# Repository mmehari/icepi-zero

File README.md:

# Icepi Zero - The portable FPGA development board

| Get your own on: | [**Crowd Supply**](https://www.crowdsupply.com/icy-electronics/icepi-zero)! | [**Elecrow**](https://www.elecrow.com/icepi-zero.html) |
| ---------------- | ------------------------ | ------------------ |

If you are a student/educational institute, send me an email at `cyao _at_ duck.com` and I'll give an educational discount of $65!

We also got a [Discord server](https://discord.gg/vzrqfhcvWr)! Feel free to ask any questions here.

## What is the Icepi Zero?

The Icepi Zero is an FPGA development board in the popular Raspberry Pi Zero form factor. It carries a Lattice ECP5 25F, enabling powerful designs while keeping a small portable size. It also has a GPDI mini (General Purpose Display Interface, same as the one on the Pi Zero) port allowing easy digital video output.

## Why Icepi Zero?

Currently most powerful FPGA boards on the market are expensive and bulky.

I've always wanted a low-cost portable FPGA with video output to make my own CPU, but there isn't any on the market.

The Icepi Zero aims to fix this. Carrying a powerful ECP5 FPGA on a small Raspberry Pi Zero form factor, it is the ultimate portable solution for FPGA development. Additionally packing a GPDI mini port and 3 USB-C ports, it allows interfacing with multiple external I/O devices.

Icepi Zero is for everyone: Students can use it to learn about the internals of modern processors. Gamers can use it to emulate old hardware. Programmers can use it to test their code on multiple architectures.

<sub>Oberon running on Icepi Zero</sub>

Icepi Zero also has an on-board USB to JTAG converter, so no external programmers are needed.

Moreover Icepi Zero is fully open-source, no strings attached. Learn from the design! ([OSHWA cerified FR000026](https://certification.oshwa.org/fr000026.html)).

## Features

- Raspberry Pi Zero form factor
- Lattice ECP5U FPGA:
    - 24k LUT
    - 112 KiB of RAM
- One MiniGPDI connector (it's HDM- but I don't have the money to buy a license...)
- Three USB-C Ports
- 256Mbit 166MHz SDRAM
- MicroSD card slot
- On-board USB to JTAG and UART converter
- 50MHz external oscillator
- 128 Mbit of flash
- 4 user LEDs
- 2 user buttons

This powerful configuration allows the PCB to be used in numerous ways, including real time video processing, hardware AI acceleration and prototyping of ASICs. 

## Emulation

Over the course of multiple weeks, multiple emulation cores have been ported over, such as the [Oberon](https://github.com/cheyao/oberon), [Apple I](https://github.com/cheyao/apple-one) and the [Acorn Atom](https://github.com/cheyao/acorn_atom)! The Icepi Zero allows you to take cycle accurate replicas of your favourite systems in your pocket.

<sub>Apple I running on the Icepi</sub>

<sub>Acorn Atom running on the Icepi</sub>

## Learning

It is also supported by icestudio (custom fork: https://github.com/cheyao/icestudio), allowing easy access for beginners.

## Usage

Check out the `firmware` folder for example code and compilation instructions!

If you want to order this board, it uses a 1.2mm/1.6mm PCB with JLC04121H-7628 Stackup. Gerbers are in the `production` folder in the `hardware` directory.

For the PCB, the smallest component size is 0201 for 27 Ohm resistors on the USB-C datalines. But if you want only 0402 components, just delete those 0201 resistors and you will be fine.

NOTE: If you fabbed v1.1 before 01/06, the pins of the USB pullups and LED0 is different - check your gerbers.

[View PCB online](https://kicanvas.org/?github=https%3A%2F%2Fgithub.com%2Fcheyao%2Ficepi-zero%2Ftree%2Fmain%2Fhardware%2Fv1.2)

## Acknowledgments

This project was inspired by the [ulx3s](https://github.com/emard/ulx3s), huge props to the ulx3s team for making such a good board!

## Contact

If there is any questions DM `cyao.` or join the [discord server](https://discord.gg/vzrqfhcvWr)! Feel free to ask any questions here. Mail is also accepted at `cyao _at_ duck.com`. :)

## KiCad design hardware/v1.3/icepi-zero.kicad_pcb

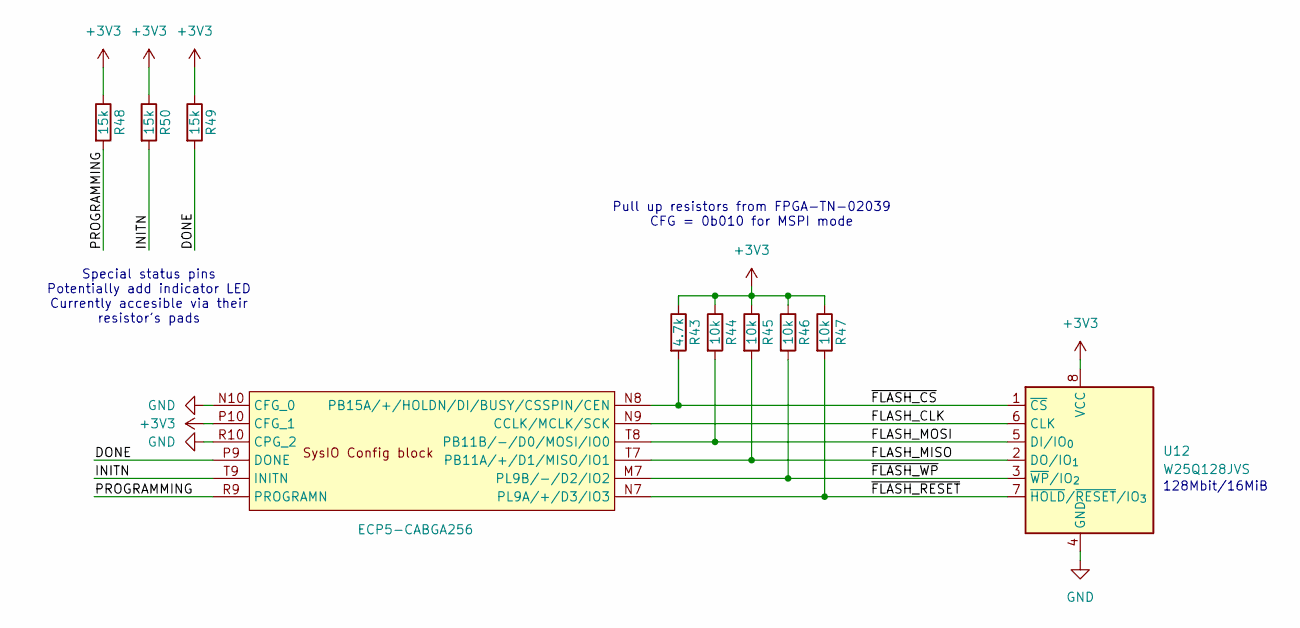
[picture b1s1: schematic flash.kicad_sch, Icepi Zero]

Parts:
R43: 4.7k; R_0402_1005Metric; Manufactuer Part Number 0402WGF4701TCE; LCSC Part # C25900
R44, R45, R46, R47: 10k; R_0402_1005Metric; Manufactuer Part Number 0402WGF1002TCE; LCSC Part # C25744
R48, R49, R50: 15k; R_0402_1005Metric; Manufactuer Part Number 0402WGF1502TCE; LCSC Part # C25756
U1: ECP5-CABGA256; BGA-256_14.0x14.0mm_Layout16x16_P0.8mm_Ball0.45mm_Pad0.32mm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; Manufactuer Part Number LFE5U-25F-6BG256C; LCSC Part # C1521614
U12: W25Q128JVS; SOIC-8_5.3x5.3mm_P1.27mm; Manufactuer Part Number W25Q128JVSIQ; LCSC Part # C97521

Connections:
+3V3: R43.1, R44.1, R45.1, R46.1, R47.1, R48.1, R49.1, R50.1, U1.P10 (CFG_1), U12.8 (VCC); also elsewhere on the board
/DBG1: U1.C7 (PT27A/+/PCLKT0_1); also elsewhere on the board
/DBG2: U1.C8 (PT35A/+/PCLKT1_0); also elsewhere on the board
/Flash/DONE: R49.2, U1.P9 (DONE)
/Flash/FLASH_CLK: U1.N9 (CCLK/MCLK/SCK), U12.6 (CLK)
/Flash/FLASH_MISO: R45.2, U1.T7 (PB11A/+/D1/MISO/IO1), U12.2 (DO/IO_{1})
/Flash/FLASH_MOSI: R44.2, U1.T8 (PB11B/-/D0/MOSI/IO0), U12.5 (DI/IO_{0})
/Flash/INITN: R50.2, U1.T9 (INITN)
/Flash/PROGRAMMING: R48.2, U1.R9 (PROGRAMN)
/Flash/~FLASH_CS: R43.2, U1.N8 (PB15A/+/HOLDN/DI/BUSY/CSSPIN/CEN), U12.1 (~CS)
/Flash/~FLASH_RESET: R47.2, U1.N7 (PL9A/+/D3/IO3), U12.7 (~HOLD/~RESET/IO_{3})
/Flash/~FLASH_WP: R46.2, U1.M7 (PL9B/-/D2/IO2), U12.3 (~WP/IO_{2})
/GLOBAL_CLK: U1.M1 (PL26C/+/LDQ32/PCLKT6_0); also elsewhere on the board
/GPIO0: U1.G3 (PL14C/+/LDQ20/VREF1_7); also elsewhere on the board
/GPIO1: U1.K3 (PL20D/-/LDQS20); also elsewhere on the board
/GPIO2: U1.T2 (PL38D/-/LDQ44); also elsewhere on the board
/GPIO3: U1.R2 (PL38C/+/LDQ44); also elsewhere on the board
/GPIO4: U1.R1 (PL35B/-/HS/LDQ32/VREF1_6); also elsewhere on the board
/GPIO5: U1.E1 (PL11D/-/LDQ8); also elsewhere on the board
/GPIO6: U1.F3 (PL5D/-/LDQ8); also elsewhere on the board
/GPIO7: U1.G1 (PL20A/+/HS/LDQS20/GR_PCLK7_1); also elsewhere on the board
/GPIO8: U1.H2 (PL20C/+/LDQS20/GR_PCLK7_0); also elsewhere on the board
/GPIO9: U1.J1 (PL23A/+/HS/LDQ20/PCLKT7); also elsewhere on the board
/GPIO10: U1.L2 (PL26B/-/HS/LDQ32/PCLKC6_1); also elsewhere on the board
/GPIO11: U1.G2 (PL14B/-/HS/LDQ20); also elsewhere on the board
/GPIO12: U1.J3 (PL20B/-/HS/LDQSN20); also elsewhere on the board
/GPIO13: U1.E3 (PL5C/+/LDQ8); also elsewhere on the board
/GPIO14: U1.P1 (PL35A/+/HS/LDQ32); also elsewhere on the board
/GPIO15: U1.N1 (PL32A/+/HS/LDQS32); also elsewhere on the board
/GPIO16: U1.H3 (PL14D/-/lDQ20); also elsewhere on the board
/GPIO17: U1.R3 (PL41B/-/HS/LDQ44); also elsewhere on the board
/GPIO18: U1.N4 (PL38A/+/HS/LDQ44); also elsewhere on the board
/GPIO19: U1.E4 (PT9A/+); also elsewhere on the board
/GPIO20: U1.F1 (PL14A/+/HS/LDQ20); also elsewhere on the board
/GPIO21: U1.F2 (PL11C/+/LDQ8); also elsewhere on the board
/GPIO22: U1.P2 (PL32B/-/HS/LDQSN32); also elsewhere on the board
/GPIO23: U1.M2 (PL26D/-/LDQ32/PCLK6_0); also elsewhere on the board
/GPIO24: U1.L1 (PL26A/+/HS/LDQ32/PCLKT6_1); also elsewhere on the board
/GPIO25: U1.J2 (PL23B/-/HS/LDQ20/PCLKC7_1); also elsewhere on the board
/GPIO26: U1.D4 (PT9B/-); also elsewhere on the board
/GPIO27: U1.P3 (PL38B/-/HS/LDQ44); also elsewhere on the board
/LED0: U1.E13 (PT62B/-); also elsewhere on the board
/LED1: U1.D14 (PR2D/-/RDQ8); also elsewhere on the board
/LED2: U1.E12 (PT58B/-); also elsewhere on the board
/LED3: U1.C13 (PT60B/-); also elsewhere on the board
/LED4: U1.D13 (PT62A/+); also elsewhere on the board
/SW0: U1.C4 (PT11A/+); also elsewhere on the board
/SW1: U1.C5 (PT15A/+); also elsewhere on the board
GND: U1.N10 (CFG_0), U1.R10 (CPG_2), U12.4 (GND); also elsewhere on the board

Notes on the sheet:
128Mbit/16MiB
Special status pins Potentially add indicator LED Currently accesible via their resistor's pads
Pull up resistors from FPGA-TN-02039 CFG = 0b010 for MSPI mode

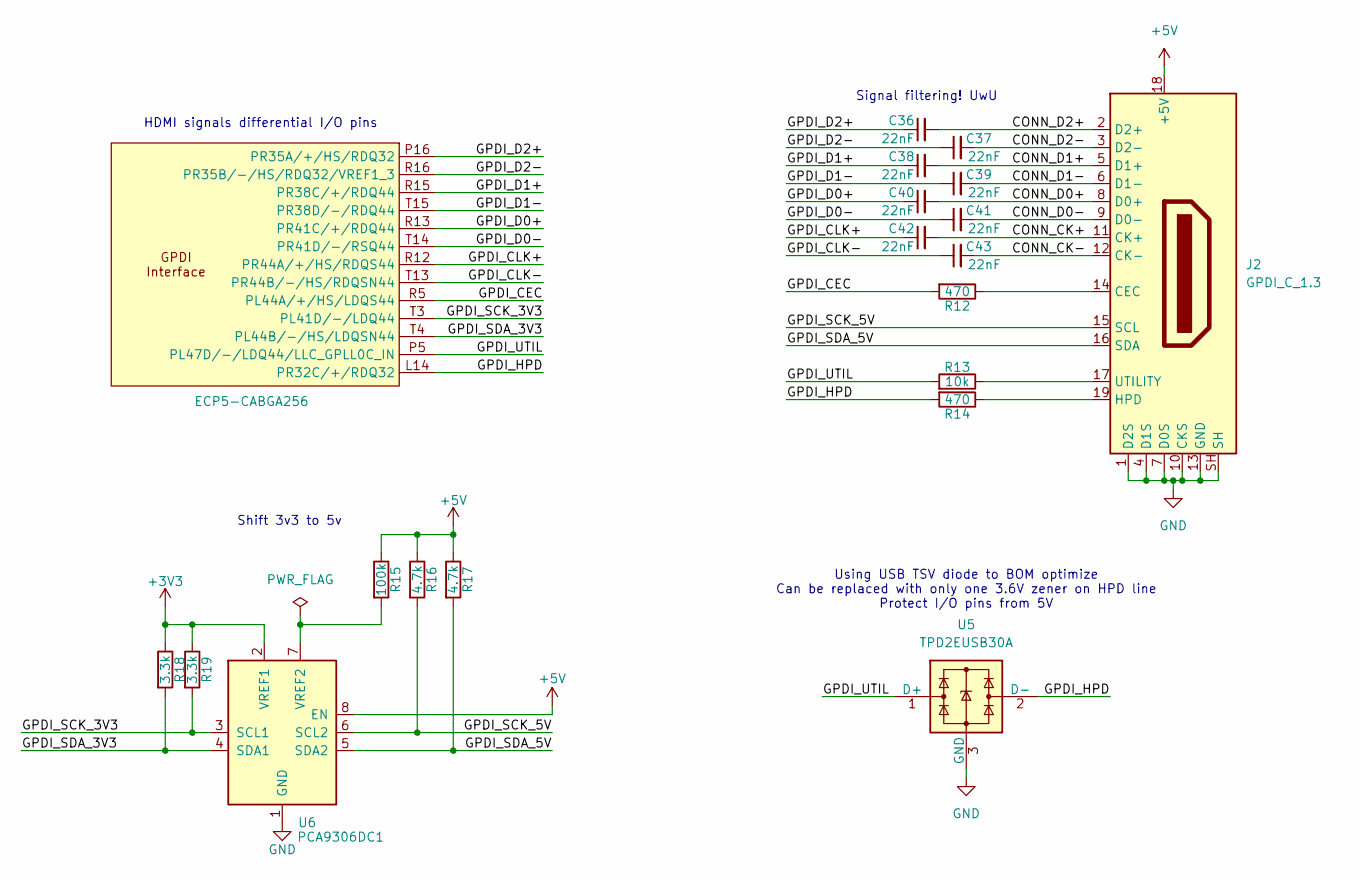
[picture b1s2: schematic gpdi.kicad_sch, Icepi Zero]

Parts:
C36, C37, C38, C39, C40, C41, C42, C43: 22nF; C_0402_1005Metric; Manufactuer Part Number 0402B223K500NT; LCSC Part # C1532
J2: GPDI_C_1.3; XKB Connection A71-05H4-111N1; Manufactuer Part Number A71-05H4-111N1; LCSC Part # C2682170
R12, R14: 470; R_0402_1005Metric; Manufactuer Part Number 0402WGF4700TCE; LCSC Part # C25117
R13: 10k; R_0402_1005Metric; Manufactuer Part Number 0402WGF1002TCE; LCSC Part # C25744
R15: 100k; R_0402_1005Metric; Manufactuer Part Number 0402WGF1003TCE; LCSC Part # C25741
R16, R17: 4.7k; R_0402_1005Metric; Manufactuer Part Number 0402WGF4701TCE; LCSC Part # C25900
R18, R19: 3.3k; R_0402_1005Metric; Manufactuer Part Number 0402WGF3301TCE; LCSC Part # C25890
U1: ECP5-CABGA256; BGA-256_14.0x14.0mm_Layout16x16_P0.8mm_Ball0.45mm_Pad0.32mm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; Manufactuer Part Number LFE5U-25F-6BG256C; LCSC Part # C1521614
U5: TPD2EUSB30A; Texas_DRT-3; Manufactuer Part Number TPD2EUSB30ADRTR; LCSC Part # C3011197
U6: PCA9306DC1; VSSOP-8_2.3x2mm_P0.5mm; Manufactuer Part Number PCA9306DC1; LCSC Part # C129510

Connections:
+3V3: R18.1, R19.1, U6.2 (VREF1); also elsewhere on the board
+5V: J2.18 (+5V), R15.1, R16.1, R17.1, U6.8 (EN); also elsewhere on the board
/DBG1: U1.C7 (PT27A/+/PCLKT0_1); also elsewhere on the board
/DBG2: U1.C8 (PT35A/+/PCLKT1_0); also elsewhere on the board
/GLOBAL_CLK: U1.M1 (PL26C/+/LDQ32/PCLKT6_0); also elsewhere on the board
/GPDI/CONN_CK+: C42.2, J2.11 (CK+)
/GPDI/CONN_CK-: C43.2, J2.12 (CK-)
/GPDI/CONN_D0+: C40.2, J2.8 (D0+)
/GPDI/CONN_D0-: C41.2, J2.9 (D0-)
/GPDI/CONN_D1+: C38.2, J2.5 (D1+)
/GPDI/CONN_D1-: C39.2, J2.6 (D1-)
/GPDI/CONN_D2+: C36.2, J2.2 (D2+)
/GPDI/CONN_D2-: C37.2, J2.3 (D2-)
/GPDI/GPDI_CEC: R12.2, U1.R5 (PL44A/+/HS/LDQS44)
/GPDI/GPDI_CLK+: C42.1, U1.R12 (PR44A/+/HS/RDQS44)
/GPDI/GPDI_CLK-: C43.1, U1.T13 (PR44B/-/HS/RDQSN44)
/GPDI/GPDI_D0+: C40.1, U1.R13 (PR41C/+/RDQ44)
/GPDI/GPDI_D0-: C41.1, U1.T14 (PR41D/-/RSQ44)
/GPDI/GPDI_D1+: C38.1, U1.R15 (PR38C/+/RDQ44)
/GPDI/GPDI_D1-: C39.1, U1.T15 (PR38D/-/RDQ44)
/GPDI/GPDI_D2+: C36.1, U1.P16 (PR35A/+/HS/RDQ32)
/GPDI/GPDI_D2-: C37.1, U1.R16 (PR35B/-/HS/RDQ32/VREF1_3)
/GPDI/GPDI_HPD: R14.2, U1.L14 (PR32C/+/RDQ32), U5.2 (D-)
/GPDI/GPDI_SCK_3V3: R19.2, U1.T3 (PL41D/-/LDQ44), U6.3 (SCL1)
/GPDI/GPDI_SCK_5V: J2.15 (SCL), R16.2, U6.6 (SCL2)
/GPDI/GPDI_SDA_3V3: R18.2, U1.T4 (PL44B/-/HS/LDQSN44), U6.4 (SDA1)
/GPDI/GPDI_SDA_5V: J2.16 (SDA), R17.2, U6.5 (SDA2)
/GPDI/GPDI_UTIL: R13.2, U1.P5 (PL47D/-/LDQ44/LLC_GPLL0C_IN), U5.1 (D+)
/GPIO0: U1.G3 (PL14C/+/LDQ20/VREF1_7); also elsewhere on the board
/GPIO1: U1.K3 (PL20D/-/LDQS20); also elsewhere on the board
/GPIO2: U1.T2 (PL38D/-/LDQ44); also elsewhere on the board
/GPIO3: U1.R2 (PL38C/+/LDQ44); also elsewhere on the board
/GPIO4: U1.R1 (PL35B/-/HS/LDQ32/VREF1_6); also elsewhere on the board
/GPIO5: U1.E1 (PL11D/-/LDQ8); also elsewhere on the board
/GPIO6: U1.F3 (PL5D/-/LDQ8); also elsewhere on the board
/GPIO7: U1.G1 (PL20A/+/HS/LDQS20/GR_PCLK7_1); also elsewhere on the board
/GPIO8: U1.H2 (PL20C/+/LDQS20/GR_PCLK7_0); also elsewhere on the board
/GPIO9: U1.J1 (PL23A/+/HS/LDQ20/PCLKT7); also elsewhere on the board
/GPIO10: U1.L2 (PL26B/-/HS/LDQ32/PCLKC6_1); also elsewhere on the board
/GPIO11: U1.G2 (PL14B/-/HS/LDQ20); also elsewhere on the board
/GPIO12: U1.J3 (PL20B/-/HS/LDQSN20); also elsewhere on the board
/GPIO13: U1.E3 (PL5C/+/LDQ8); also elsewhere on the board
/GPIO14: U1.P1 (PL35A/+/HS/LDQ32); also elsewhere on the board
/GPIO15: U1.N1 (PL32A/+/HS/LDQS32); also elsewhere on the board
/GPIO16: U1.H3 (PL14D/-/lDQ20); also elsewhere on the board
/GPIO17: U1.R3 (PL41B/-/HS/LDQ44); also elsewhere on the board
/GPIO18: U1.N4 (PL38A/+/HS/LDQ44); also elsewhere on the board
/GPIO19: U1.E4 (PT9A/+); also elsewhere on the board
/GPIO20: U1.F1 (PL14A/+/HS/LDQ20); also elsewhere on the board
/GPIO21: U1.F2 (PL11C/+/LDQ8); also elsewhere on the board
/GPIO22: U1.P2 (PL32B/-/HS/LDQSN32); also elsewhere on the board
/GPIO23: U1.M2 (PL26D/-/LDQ32/PCLK6_0); also elsewhere on the board
/GPIO24: U1.L1 (PL26A/+/HS/LDQ32/PCLKT6_1); also elsewhere on the board
/GPIO25: U1.J2 (PL23B/-/HS/LDQ20/PCLKC7_1); also elsewhere on the board
/GPIO26: U1.D4 (PT9B/-); also elsewhere on the board
/GPIO27: U1.P3 (PL38B/-/HS/LDQ44); also elsewhere on the board
/LED0: U1.E13 (PT62B/-); also elsewhere on the board
/LED1: U1.D14 (PR2D/-/RDQ8); also elsewhere on the board
/LED2: U1.E12 (PT58B/-); also elsewhere on the board
/LED3: U1.C13 (PT60B/-); also elsewhere on the board
/LED4: U1.D13 (PT62A/+); also elsewhere on the board
/SW0: U1.C4 (PT11A/+); also elsewhere on the board
/SW1: U1.C5 (PT15A/+); also elsewhere on the board
GND: J2.1 (D2S), J2.4 (D1S), J2.7 (D0S), J2.10 (CKS), J2.13 (GND), J2.SH, U5.3 (GND), U6.1 (GND); also elsewhere on the board
unnamed: J2.14 (CEC), R12.1
unnamed: J2.19 (HPD), R14.1
unnamed: J2.17 (UTILITY), R13.1
unnamed: R15.2, U6.7 (VREF2)

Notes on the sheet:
Shift 3v3 to 5v
Using USB TSV diode to BOM optimize Can be replaced with only one 3.6V zener on HPD line Protect I/O pins from 5V
HDMI signals differential I/O pins
Signal filtering! UwU

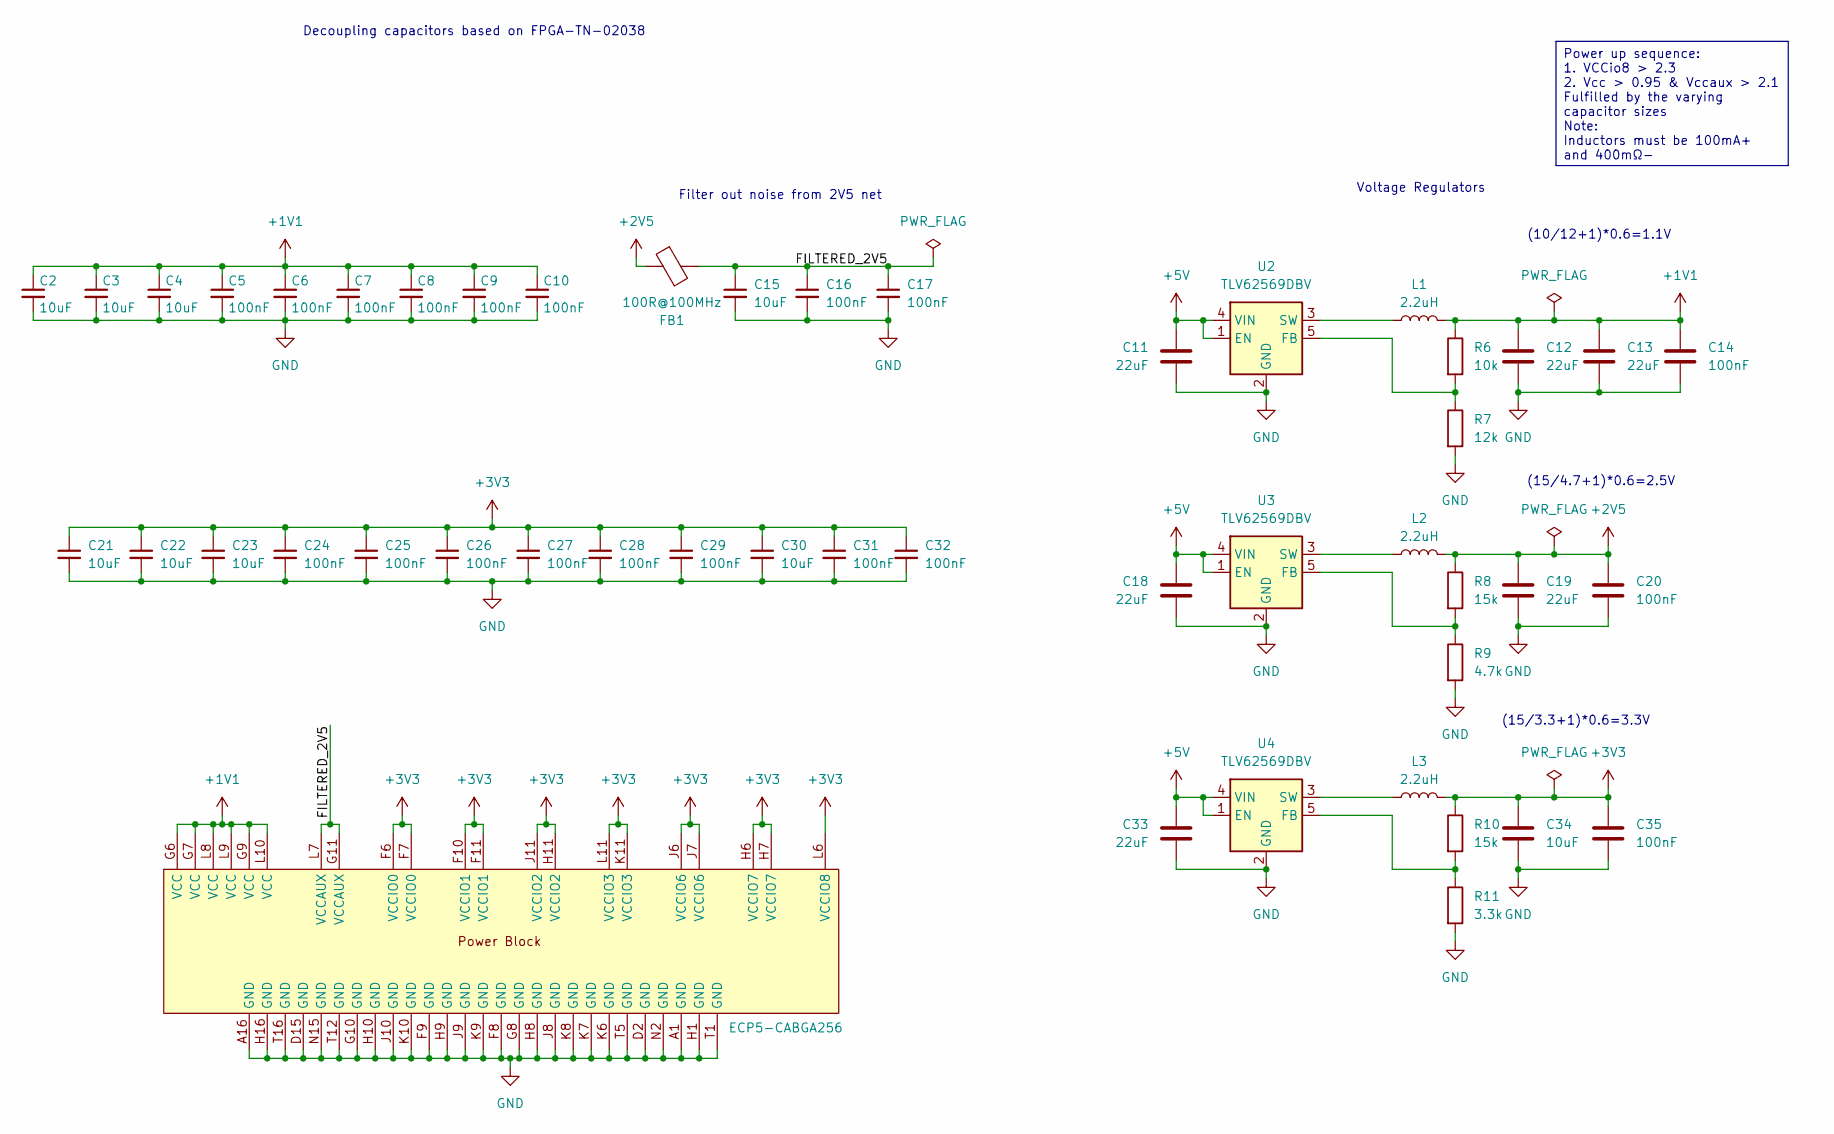
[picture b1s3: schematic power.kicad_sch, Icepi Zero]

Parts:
C2, C3, C4, C15, C21, C22, C23, C30, C34: 10uF; C_0603_1608Metric; Manufactuer Part Number CL10A106KP8NNNC; LCSC Part # C19702
C5, C6, C7, C8, C9, C10, C14, C16, C17, C20, C24, C25, C26, C27, C28, C29, C31, C32, C35: 100nF; C_0402_1005Metric; Manufactuer Part Number CL05B104KB54PNC; LCSC Part # C307331
C11, C12, C13, C18, C19, C33: 22uF; C_0603_1608Metric; Manufactuer Part Number CL10A226MQ8NRNC; LCSC Part # C59461
FB1: 100R@100MHz; L_0805_2012Metric; Manufactuer Part Number CBG201209U101T; LCSC Part # C74480
L1, L2, L3: 2.2uH; L_0805_2012Metric; Manufactuer Part Number TDK MLP2012S2R2MT0S1; LCSC Part # C107322
R6: 10k; R_0402_1005Metric; Manufactuer Part Number 0402WGF1002TCE; LCSC Part # C25744
R7: 12k; R_0402_1005Metric; Manufactuer Part Number 0402WGF1202TCE; LCSC Part # C25752
R8, R10: 15k; R_0402_1005Metric; Manufactuer Part Number 0402WGF1502TCE; LCSC Part # C25756
R9: 4.7k; R_0402_1005Metric; Manufactuer Part Number 0402WGF4701TCE; LCSC Part # C25900
R11: 3.3k; R_0402_1005Metric; Manufactuer Part Number 0402WGF3301TCE; LCSC Part # C25890
U1: ECP5-CABGA256; BGA-256_14.0x14.0mm_Layout16x16_P0.8mm_Ball0.45mm_Pad0.32mm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; Manufactuer Part Number LFE5U-25F-6BG256C; LCSC Part # C1521614
U2, U3, U4: TLV62569DBV; SOT-23-5; Manufactuer Part Number TLV62569DBVR; LCSC Part # C141836

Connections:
+1V1: C2.1, C3.1, C4.1, C5.1, C6.1, C7.1, C8.1, C9.1, C10.1, C12.1, C13.1, C14.1, L1.2, R6.1, U1.G6 (VCC), U1.G7 (VCC), U1.G9 (VCC), U1.L8 (VCC), U1.L9 (VCC), U1.L10 (VCC); also elsewhere on the board
+2V5: C19.1, C20.1, FB1.1, L2.2, R8.1; also elsewhere on the board
+3V3: C21.1, C22.1, C23.1, C24.1, C25.1, C26.1, C27.1, C28.1, C29.1, C30.1, C31.1, C32.1, C34.1, C35.1, L3.2, R10.1, U1.F6 (VCCIO0), U1.F7 (VCCIO0), U1.F10 (VCCIO1), U1.F11 (VCCIO1), U1.H6 (VCCIO7), U1.H7 (VCCIO7), U1.H11 (VCCIO2), U1.J6 (VCCIO6), U1.J7 (VCCIO6), U1.J11 (VCCIO2), U1.K11 (VCCIO3), U1.L6 (VCCIO8), U1.L11 (VCCIO3); also elsewhere on the board
+5V: C11.1, C18.1, C33.1, U2.1 (EN), U2.4 (VIN), U3.1 (EN), U3.4 (VIN), U4.1 (EN), U4.4 (VIN); also elsewhere on the board
/DBG1: U1.C7 (PT27A/+/PCLKT0_1); also elsewhere on the board
/DBG2: U1.C8 (PT35A/+/PCLKT1_0); also elsewhere on the board
/GLOBAL_CLK: U1.M1 (PL26C/+/LDQ32/PCLKT6_0); also elsewhere on the board
/GPIO0: U1.G3 (PL14C/+/LDQ20/VREF1_7); also elsewhere on the board
/GPIO1: U1.K3 (PL20D/-/LDQS20); also elsewhere on the board
/GPIO2: U1.T2 (PL38D/-/LDQ44); also elsewhere on the board
/GPIO3: U1.R2 (PL38C/+/LDQ44); also elsewhere on the board
/GPIO4: U1.R1 (PL35B/-/HS/LDQ32/VREF1_6); also elsewhere on the board
/GPIO5: U1.E1 (PL11D/-/LDQ8); also elsewhere on the board
/GPIO6: U1.F3 (PL5D/-/LDQ8); also elsewhere on the board
/GPIO7: U1.G1 (PL20A/+/HS/LDQS20/GR_PCLK7_1); also elsewhere on the board
/GPIO8: U1.H2 (PL20C/+/LDQS20/GR_PCLK7_0); also elsewhere on the board
/GPIO9: U1.J1 (PL23A/+/HS/LDQ20/PCLKT7); also elsewhere on the board
/GPIO10: U1.L2 (PL26B/-/HS/LDQ32/PCLKC6_1); also elsewhere on the board
/GPIO11: U1.G2 (PL14B/-/HS/LDQ20); also elsewhere on the board
/GPIO12: U1.J3 (PL20B/-/HS/LDQSN20); also elsewhere on the board
/GPIO13: U1.E3 (PL5C/+/LDQ8); also elsewhere on the board
/GPIO14: U1.P1 (PL35A/+/HS/LDQ32); also elsewhere on the board
/GPIO15: U1.N1 (PL32A/+/HS/LDQS32); also elsewhere on the board
/GPIO16: U1.H3 (PL14D/-/lDQ20); also elsewhere on the board
/GPIO17: U1.R3 (PL41B/-/HS/LDQ44); also elsewhere on the board
/GPIO18: U1.N4 (PL38A/+/HS/LDQ44); also elsewhere on the board
/GPIO19: U1.E4 (PT9A/+); also elsewhere on the board
/GPIO20: U1.F1 (PL14A/+/HS/LDQ20); also elsewhere on the board
/GPIO21: U1.F2 (PL11C/+/LDQ8); also elsewhere on the board
/GPIO22: U1.P2 (PL32B/-/HS/LDQSN32); also elsewhere on the board
/GPIO23: U1.M2 (PL26D/-/LDQ32/PCLK6_0); also elsewhere on the board
/GPIO24: U1.L1 (PL26A/+/HS/LDQ32/PCLKT6_1); also elsewhere on the board
/GPIO25: U1.J2 (PL23B/-/HS/LDQ20/PCLKC7_1); also elsewhere on the board
/GPIO26: U1.D4 (PT9B/-); also elsewhere on the board
/GPIO27: U1.P3 (PL38B/-/HS/LDQ44); also elsewhere on the board
/LED0: U1.E13 (PT62B/-); also elsewhere on the board
/LED1: U1.D14 (PR2D/-/RDQ8); also elsewhere on the board
/LED2: U1.E12 (PT58B/-); also elsewhere on the board
/LED3: U1.C13 (PT60B/-); also elsewhere on the board
/LED4: U1.D13 (PT62A/+); also elsewhere on the board
/Power/FILTERED_2V5: C15.1, C16.1, C17.1, FB1.2, U1.G11 (VCCAUX), U1.L7 (VCCAUX)
/SW0: U1.C4 (PT11A/+); also elsewhere on the board
/SW1: U1.C5 (PT15A/+); also elsewhere on the board
GND: C2.2, C3.2, C4.2, C5.2, C6.2, C7.2, C8.2, C9.2, C10.2, C11.2, C12.2, C13.2, C14.2, C15.2, C16.2, C17.2, C18.2, C19.2, C20.2, C21.2, C22.2, C23.2, C24.2, C25.2, C26.2, C27.2, C28.2, C29.2, C30.2, C31.2, C32.2, C33.2, C34.2, C35.2, R7.2, R9.2, R11.2, U1.A1 (GND), U1.A16 (GND), U1.D2 (GND), U1.D15 (GND), U1.F8 (GND), U1.F9 (GND), U1.G8 (GND), U1.G10 (GND), U1.H1 (GND), U1.H8 (GND), U1.H9 (GND), U1.H10 (GND), U1.H16 (GND), U1.J8 (GND), U1.J9 (GND), U1.J10 (GND), U1.K6 (GND), U1.K7 (GND), U1.K8 (GND), U1.K9 (GND), U1.K10 (GND), U1.N2 (GND), U1.N15 (GND), U1.T1 (GND), U1.T5 (GND), U1.T12 (GND), U1.T16 (GND), U2.2 (GND), U3.2 (GND), U4.2 (GND); also elsewhere on the board
unnamed: R6.2, R7.1, U2.5 (FB)
unnamed: L1.1, U2.3 (SW)
unnamed: R8.2, R9.1, U3.5 (FB)
unnamed: L2.1, U3.3 (SW)
unnamed: R10.2, R11.1, U4.5 (FB)
unnamed: L3.1, U4.3 (SW)

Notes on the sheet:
Decoupling capacitors based on FPGA-TN-02038
(15/4.7+1)*0.6=2.5V
(10/12+1)*0.6=1.1V
Filter out noise from 2V5 net
(15/3.3+1)*0.6=3.3V
Voltage Regulators
Power up sequence: 1. VCCio8 > 2.3 2. Vcc > 0.95 & Vccaux > 2.1 Fulfilled by the varying capacitor sizes Note: Inductors must be 100mA+ and 400mΩ-

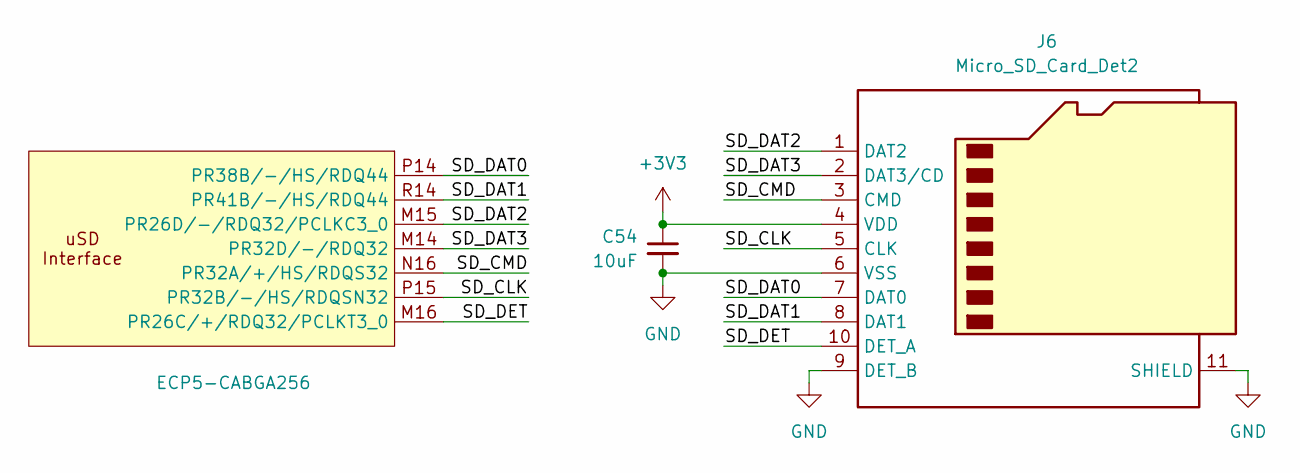
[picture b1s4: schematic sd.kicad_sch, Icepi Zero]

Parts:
C54: 10uF; C_0603_1608Metric; Manufactuer Part Number CL10A106KP8NNNC; LCSC Part # C19702
J6: Micro_SD_Card_Det2; microSD_HC_SOFNG_TF-008; Manufactuer Part Number TF-008; LCSC Part # C428465
U1: ECP5-CABGA256; BGA-256_14.0x14.0mm_Layout16x16_P0.8mm_Ball0.45mm_Pad0.32mm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; Manufactuer Part Number LFE5U-25F-6BG256C; LCSC Part # C1521614

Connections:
+3V3: C54.1, J6.4 (VDD); also elsewhere on the board
/DBG1: U1.C7 (PT27A/+/PCLKT0_1); also elsewhere on the board
/DBG2: U1.C8 (PT35A/+/PCLKT1_0); also elsewhere on the board
/GLOBAL_CLK: U1.M1 (PL26C/+/LDQ32/PCLKT6_0); also elsewhere on the board
/GPIO0: U1.G3 (PL14C/+/LDQ20/VREF1_7); also elsewhere on the board
/GPIO1: U1.K3 (PL20D/-/LDQS20); also elsewhere on the board
/GPIO2: U1.T2 (PL38D/-/LDQ44); also elsewhere on the board
/GPIO3: U1.R2 (PL38C/+/LDQ44); also elsewhere on the board
/GPIO4: U1.R1 (PL35B/-/HS/LDQ32/VREF1_6); also elsewhere on the board
/GPIO5: U1.E1 (PL11D/-/LDQ8); also elsewhere on the board
/GPIO6: U1.F3 (PL5D/-/LDQ8); also elsewhere on the board
/GPIO7: U1.G1 (PL20A/+/HS/LDQS20/GR_PCLK7_1); also elsewhere on the board
/GPIO8: U1.H2 (PL20C/+/LDQS20/GR_PCLK7_0); also elsewhere on the board
/GPIO9: U1.J1 (PL23A/+/HS/LDQ20/PCLKT7); also elsewhere on the board
/GPIO10: U1.L2 (PL26B/-/HS/LDQ32/PCLKC6_1); also elsewhere on the board
/GPIO11: U1.G2 (PL14B/-/HS/LDQ20); also elsewhere on the board
/GPIO12: U1.J3 (PL20B/-/HS/LDQSN20); also elsewhere on the board
/GPIO13: U1.E3 (PL5C/+/LDQ8); also elsewhere on the board
/GPIO14: U1.P1 (PL35A/+/HS/LDQ32); also elsewhere on the board
/GPIO15: U1.N1 (PL32A/+/HS/LDQS32); also elsewhere on the board
/GPIO16: U1.H3 (PL14D/-/lDQ20); also elsewhere on the board
/GPIO17: U1.R3 (PL41B/-/HS/LDQ44); also elsewhere on the board
/GPIO18: U1.N4 (PL38A/+/HS/LDQ44); also elsewhere on the board
/GPIO19: U1.E4 (PT9A/+); also elsewhere on the board
/GPIO20: U1.F1 (PL14A/+/HS/LDQ20); also elsewhere on the board
/GPIO21: U1.F2 (PL11C/+/LDQ8); also elsewhere on the board
/GPIO22: U1.P2 (PL32B/-/HS/LDQSN32); also elsewhere on the board
/GPIO23: U1.M2 (PL26D/-/LDQ32/PCLK6_0); also elsewhere on the board
/GPIO24: U1.L1 (PL26A/+/HS/LDQ32/PCLKT6_1); also elsewhere on the board
/GPIO25: U1.J2 (PL23B/-/HS/LDQ20/PCLKC7_1); also elsewhere on the board
/GPIO26: U1.D4 (PT9B/-); also elsewhere on the board
/GPIO27: U1.P3 (PL38B/-/HS/LDQ44); also elsewhere on the board
/LED0: U1.E13 (PT62B/-); also elsewhere on the board
/LED1: U1.D14 (PR2D/-/RDQ8); also elsewhere on the board
/LED2: U1.E12 (PT58B/-); also elsewhere on the board
/LED3: U1.C13 (PT60B/-); also elsewhere on the board
/LED4: U1.D13 (PT62A/+); also elsewhere on the board
/SW0: U1.C4 (PT11A/+); also elsewhere on the board
/SW1: U1.C5 (PT15A/+); also elsewhere on the board
/uSD/SD_CLK: J6.5 (CLK), U1.P15 (PR32B/-/HS/RDQSN32)
/uSD/SD_CMD: J6.3 (CMD), U1.N16 (PR32A/+/HS/RDQS32)
/uSD/SD_DAT0: J6.7 (DAT0), U1.P14 (PR38B/-/HS/RDQ44)
/uSD/SD_DAT1: J6.8 (DAT1), U1.R14 (PR41B/-/HS/RDQ44)
/uSD/SD_DAT2: J6.1 (DAT2), U1.M15 (PR26D/-/RDQ32/PCLKC3_0)
/uSD/SD_DAT3: J6.2 (DAT3/CD), U1.M14 (PR32D/-/RDQ32)
/uSD/SD_DET: J6.10 (DET_A), U1.M16 (PR26C/+/RDQ32/PCLKT3_0)
GND: C54.2, J6.6 (VSS), J6.9 (DET_B), J6.11 (SHIELD); also elsewhere on the board

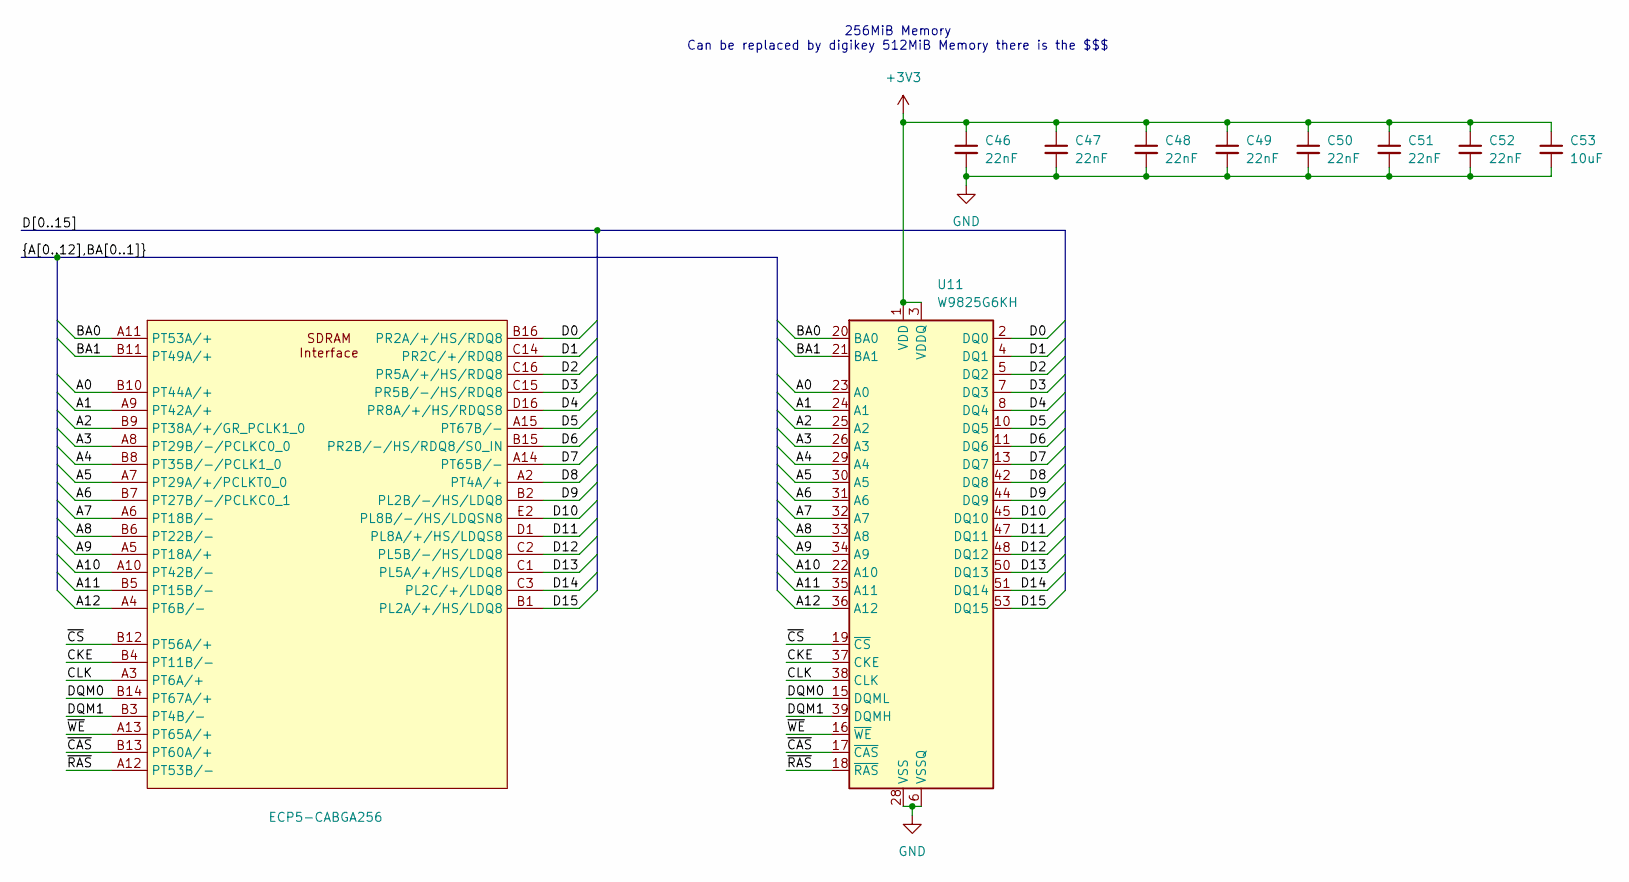
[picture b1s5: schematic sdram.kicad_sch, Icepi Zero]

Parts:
C46, C47, C48, C49, C50, C51, C52: 22nF; C_0603_1608Metric; Manufactuer Part Number 0603B223K500NT; LCSC Part # C77571
C53: 10uF; C_0603_1608Metric; Manufactuer Part Number CL10A106KP8NNNC; LCSC Part # C19702
U1: ECP5-CABGA256; BGA-256_14.0x14.0mm_Layout16x16_P0.8mm_Ball0.45mm_Pad0.32mm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; Manufactuer Part Number LFE5U-25F-6BG256C; LCSC Part # C1521614
U11: W9825G6KH; TSOP-II-54_22.2x10.16mm_P0.8mm; Manufactuer Part Number W9825G6KH-6; LCSC Part # C62246

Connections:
+3V3: C46.1, C47.1, C48.1, C49.1, C50.1, C51.1, C52.1, C53.1, U11.1 (VDD), U11.3 (VDDQ), U11.9 (VDDQ), U11.14 (VDD), U11.27 (VDD), U11.43 (VDDQ), U11.49 (VDDQ); also elsewhere on the board
/DBG1: U1.C7 (PT27A/+/PCLKT0_1); also elsewhere on the board
/DBG2: U1.C8 (PT35A/+/PCLKT1_0); also elsewhere on the board
/GLOBAL_CLK: U1.M1 (PL26C/+/LDQ32/PCLKT6_0); also elsewhere on the board
/GPIO0: U1.G3 (PL14C/+/LDQ20/VREF1_7); also elsewhere on the board
/GPIO1: U1.K3 (PL20D/-/LDQS20); also elsewhere on the board
/GPIO2: U1.T2 (PL38D/-/LDQ44); also elsewhere on the board
/GPIO3: U1.R2 (PL38C/+/LDQ44); also elsewhere on the board
/GPIO4: U1.R1 (PL35B/-/HS/LDQ32/VREF1_6); also elsewhere on the board
/GPIO5: U1.E1 (PL11D/-/LDQ8); also elsewhere on the board
/GPIO6: U1.F3 (PL5D/-/LDQ8); also elsewhere on the board
/GPIO7: U1.G1 (PL20A/+/HS/LDQS20/GR_PCLK7_1); also elsewhere on the board
/GPIO8: U1.H2 (PL20C/+/LDQS20/GR_PCLK7_0); also elsewhere on the board
/GPIO9: U1.J1 (PL23A/+/HS/LDQ20/PCLKT7); also elsewhere on the board
/GPIO10: U1.L2 (PL26B/-/HS/LDQ32/PCLKC6_1); also elsewhere on the board
/GPIO11: U1.G2 (PL14B/-/HS/LDQ20); also elsewhere on the board
/GPIO12: U1.J3 (PL20B/-/HS/LDQSN20); also elsewhere on the board
/GPIO13: U1.E3 (PL5C/+/LDQ8); also elsewhere on the board
/GPIO14: U1.P1 (PL35A/+/HS/LDQ32); also elsewhere on the board
/GPIO15: U1.N1 (PL32A/+/HS/LDQS32); also elsewhere on the board
/GPIO16: U1.H3 (PL14D/-/lDQ20); also elsewhere on the board
/GPIO17: U1.R3 (PL41B/-/HS/LDQ44); also elsewhere on the board
/GPIO18: U1.N4 (PL38A/+/HS/LDQ44); also elsewhere on the board
/GPIO19: U1.E4 (PT9A/+); also elsewhere on the board
/GPIO20: U1.F1 (PL14A/+/HS/LDQ20); also elsewhere on the board
/GPIO21: U1.F2 (PL11C/+/LDQ8); also elsewhere on the board
/GPIO22: U1.P2 (PL32B/-/HS/LDQSN32); also elsewhere on the board
/GPIO23: U1.M2 (PL26D/-/LDQ32/PCLK6_0); also elsewhere on the board
/GPIO24: U1.L1 (PL26A/+/HS/LDQ32/PCLKT6_1); also elsewhere on the board
/GPIO25: U1.J2 (PL23B/-/HS/LDQ20/PCLKC7_1); also elsewhere on the board
/GPIO26: U1.D4 (PT9B/-); also elsewhere on the board
/GPIO27: U1.P3 (PL38B/-/HS/LDQ44); also elsewhere on the board
/LED0: U1.E13 (PT62B/-); also elsewhere on the board
/LED1: U1.D14 (PR2D/-/RDQ8); also elsewhere on the board
/LED2: U1.E12 (PT58B/-); also elsewhere on the board
/LED3: U1.C13 (PT60B/-); also elsewhere on the board
/LED4: U1.D13 (PT62A/+); also elsewhere on the board
/SDRAM/A0: U1.B10 (PT44A/+), U11.23 (A0)
/SDRAM/A1: U1.A9 (PT42A/+), U11.24 (A1)
/SDRAM/A2: U1.B9 (PT38A/+/GR_PCLK1_0), U11.25 (A2)
/SDRAM/A3: U1.A8 (PT29B/-/PCLKC0_0), U11.26 (A3)
/SDRAM/A4: U1.B8 (PT35B/-/PCLK1_0), U11.29 (A4)
/SDRAM/A5: U1.A7 (PT29A/+/PCLKT0_0), U11.30 (A5)
/SDRAM/A6: U1.B7 (PT27B/-/PCLKC0_1), U11.31 (A6)
/SDRAM/A7: U1.A6 (PT18B/-), U11.32 (A7)
/SDRAM/A8: U1.B6 (PT22B/-), U11.33 (A8)
/SDRAM/A9: U1.A5 (PT18A/+), U11.34 (A9)
/SDRAM/A10: U1.A10 (PT42B/-), U11.22 (A10)
/SDRAM/A11: U1.B5 (PT15B/-), U11.35 (A11)
/SDRAM/A12: U1.A4 (PT6B/-), U11.36 (A12)
/SDRAM/BA0: U1.A11 (PT53A/+), U11.20 (BA0)
/SDRAM/BA1: U1.B11 (PT49A/+), U11.21 (BA1)
/SDRAM/CKE: U1.B4 (PT11B/-), U11.37 (CKE)
/SDRAM/CLK: U1.A3 (PT6A/+), U11.38 (CLK)
/SDRAM/D0: U1.B16 (PR2A/+/HS/RDQ8), U11.2 (DQ0)
/SDRAM/D1: U1.C14 (PR2C/+/RDQ8), U11.4 (DQ1)
/SDRAM/D2: U1.C16 (PR5A/+/HS/RDQ8), U11.5 (DQ2)
/SDRAM/D3: U1.C15 (PR5B/-/HS/RDQ8), U11.7 (DQ3)
/SDRAM/D4: U1.D16 (PR8A/+/HS/RDQS8), U11.8 (DQ4)
/SDRAM/D5: U1.A15 (PT67B/-), U11.10 (DQ5)
/SDRAM/D6: U1.B15 (PR2B/-/HS/RDQ8/S0_IN), U11.11 (DQ6)
/SDRAM/D7: U1.A14 (PT65B/-), U11.13 (DQ7)
/SDRAM/D8: U1.A2 (PT4A/+), U11.42 (DQ8)
/SDRAM/D9: U1.B2 (PL2B/-/HS/LDQ8), U11.44 (DQ9)
/SDRAM/D10: U1.E2 (PL8B/-/HS/LDQSN8), U11.45 (DQ10)
/SDRAM/D11: U1.D1 (PL8A/+/HS/LDQS8), U11.47 (DQ11)
/SDRAM/D12: U1.C2 (PL5B/-/HS/LDQ8), U11.48 (DQ12)
/SDRAM/D13: U1.C1 (PL5A/+/HS/LDQ8), U11.50 (DQ13)
/SDRAM/D14: U1.C3 (PL2C/+/LDQ8), U11.51 (DQ14)
/SDRAM/D15: U1.B1 (PL2A/+/HS/LDQ8), U11.53 (DQ15)
/SDRAM/DQM0: U1.B14 (PT67A/+), U11.15 (DQML)
/SDRAM/DQM1: U1.B3 (PT4B/-), U11.39 (DQMH)
/SDRAM/~CAS: U1.B13 (PT60A/+), U11.17 (~CAS)
/SDRAM/~CS: U1.B12 (PT56A/+), U11.19 (~CS)
/SDRAM/~RAS: U1.A12 (PT53B/-), U11.18 (~RAS)
/SDRAM/~WE: U1.A13 (PT65A/+), U11.16 (~WE)
/SW0: U1.C4 (PT11A/+); also elsewhere on the board
/SW1: U1.C5 (PT15A/+); also elsewhere on the board
GND: C46.2, C47.2, C48.2, C49.2, C50.2, C51.2, C52.2, C53.2, U11.6 (VSSQ), U11.12 (VSSQ), U11.28 (VSS), U11.41 (VSS), U11.46 (VSSQ), U11.52 (VSSQ), U11.54 (VSS); also elsewhere on the board

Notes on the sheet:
256MiB Memory Can be replaced by digikey 512MiB Memory there is the $$$

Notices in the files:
hardware/v1.3/flash.kicad_sch:
License: Solderpad
